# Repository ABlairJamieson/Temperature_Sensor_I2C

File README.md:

# I2C Temperature Sensor Board

Small TMP117 temperature-sensor board for the custom Radxa CM5 camera carrier.
The intended use is remote temperature monitoring, including the camera FPGA
area. Two boards can connect using separate cables to the carrier's two
parallel I2C connectors, provided each sensor has a different address.

## KiCad project

Open `Temperature Sensor I2C.kicad_pro` in KiCad 10.

- `Temperature Sensor I2C.kicad_sch`: schematic.
- `Temperature Sensor I2C.kicad_pcb`: routed PCB.
- `includes/TMP117AIDRVR/`: custom symbol, footprint and STEP model.
- `sym-lib-table` and `fp-lib-table`: project-relative library definitions.

Local history, automatic backups, editor preferences and generated `jlcpcb/`
outputs are excluded from Git. Regenerate manufacturing outputs from the
intended design revision before ordering.

## Power and connector

Use **3.3 V power and 3.3 V I2C signals** with the matching carrier.
Do not connect this board to the camera's 12 V supply.

J1 is a four-pin JST-PH, 2.00 mm pitch, vertical header
(`B4B-PH-K` footprint):

| Pin | Signal |
| --- | --- |
| 1 | +3V3 |
| 2 | I2C SDA |
| 3 | I2C SCL |
| 4 | GND |

Verify cable continuity by pin number: **1-to-1, 2-to-2, 3-to-3, 4-to-4**.
Do not rely solely on wire colours or the apparent connector orientation.
Disconnect power before connecting or changing cables.

There are no SDA/SCL pull-up resistors on this sensor board; the matching CM5
carrier supplies them. For another host, provide suitable pull-ups to 3.3 V.
Keep cables short and start testing at 100 kHz.

## I2C address selection

Fit **exactly one** of the four zero-ohm address resistors. Leave all others
unpopulated (DNP). Fitting more than one can short supply or bus signals.

| Fit only | ADD0 connection | 7-bit address |
| --- | --- | --- |
| R3 | GND | `0x48` |
| R4 | +3V3 | `0x49` |
| R1 | SDA | `0x4A` |
| R2 | SCL | `0x4B` |

The saved schematic populates **R3 only**, selecting `0x48`.
For two sensors, assemble one with R3 only and the other with R4 only.
These addresses do not overlap the carrier's INA226 monitors (`0x40`, `0x41`).
Check the assembly BOM/DNP settings for each sensor variant before ordering.

## Assembly and mounting

- U1: TMP117AIDRVR, WSON package.
- C1: 10 uF supply capacitor; C2: 100 nF supply bypass.
- ALERT is unused; the exposed thermal pad is electrically unconnected.
- The thermal pad should remain unsoldered for best accuracy on a rigid PCB,
  as recommended by TI. Preserve the footprint's intentional lack of a
  centre-pad paste opening.
- Ensure components do not obstruct the intended thermal-contact surface.
  Use electrically insulating thermal interface material where needed; do not
  allow board copper or connector pins to short the camera electronics.
- This measures the sensor's temperature. Contact, airflow and mounting affect
  how closely that represents the FPGA/package temperature.

## Initial check

1. Verify the fitted address resistor and cable pinout with power disconnected.
2. Connect to the carrier and confirm 3.3 V between J1 pins 1 and 4.
3. Enable the appropriate I2C controller/pinmux on the CM5. Determine the actual
   Linux bus using `i2cdetect -l`; do not assume a fixed bus number.
4. Confirm communication at the selected address and read temperature using a
   TMP117-compatible driver/application. Allow the first conversion to finish.
5. With two sensors attached, verify both addresses and gently warm one board
   to establish which software channel corresponds to each physical sensor.

Hardware checks do not replace testing an assembled board and its actual cables.

## References

- [TI TMP117 datasheet](https://www.ti.com/lit/ds/symlink/tmp117.pdf): pinout,
  address selection, register interface and thermal-layout guidance.
- [Matching CM5 carrier](https://github.com/ABlairJamieson/cm5_carrier):
  see the `v1_1_power` design branch.

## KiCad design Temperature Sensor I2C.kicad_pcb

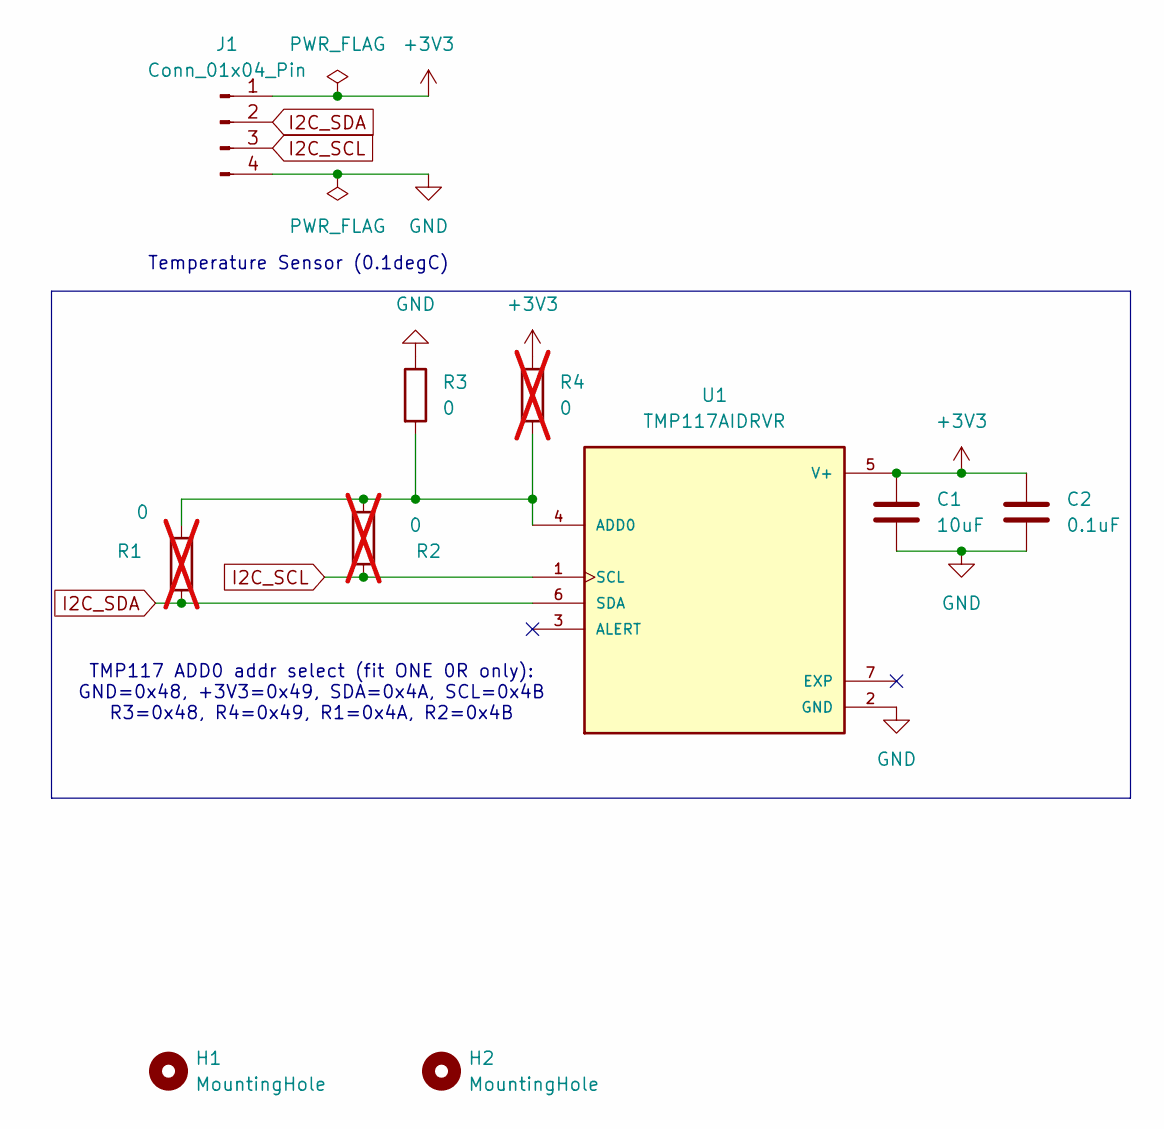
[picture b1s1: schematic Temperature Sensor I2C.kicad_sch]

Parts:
C1: 10uF; C_0805_2012Metric
C2: 0.1uF; C_0402_1005Metric
H1, H2: MountingHole; MountingHole_3.2mm_M3
J1: Conn_01x04_Pin; JST_PH_B4B-PH-K_1x04_P2.00mm_Vertical
R1, R2, R4: 0; R_0603_1608Metric; not fitted
R3: 0; R_0603_1608Metric
U1: TMP117AIDRVR; SON65P200X200X80-7N; PARTREV B; DigiKey_Part_Number 296-51834-1-ND

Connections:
+3V3: C1.1, C2.1, J1.1, R4.1, U1.5 (V+)
GND: C1.2, C2.2, J1.4, R3.1, U1.2 (GND)
I2C_SCL: J1.3, R2.1, U1.1 (SCL)
I2C_SDA: J1.2, R1.1, U1.6 (SDA)
unnamed: R1.2, R2.2, R3.2, R4.2, U1.4 (ADD0)

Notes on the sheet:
Temperature Sensor (0.1degC)
TMP117 ADD0 addr select (fit ONE 0R only): GND=0x48, +3V3=0x49, SDA=0x4A, SCL=0x4B R3=0x48, R4=0x49, R1=0x4A, R2=0x4B

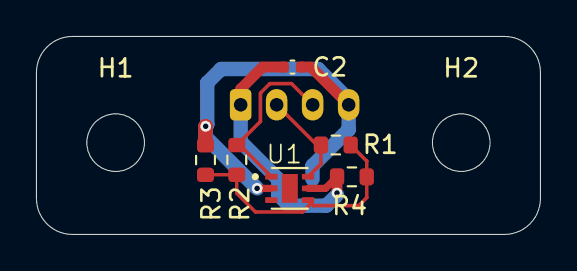
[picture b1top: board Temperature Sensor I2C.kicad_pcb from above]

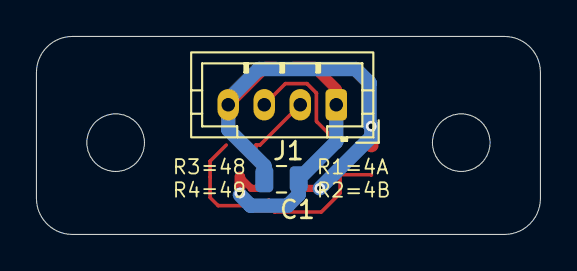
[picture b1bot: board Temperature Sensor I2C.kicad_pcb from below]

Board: 2 copper layers, 28.0 x 11.0 mm, 10 parts (2 on the bottom side), 5 nets.
